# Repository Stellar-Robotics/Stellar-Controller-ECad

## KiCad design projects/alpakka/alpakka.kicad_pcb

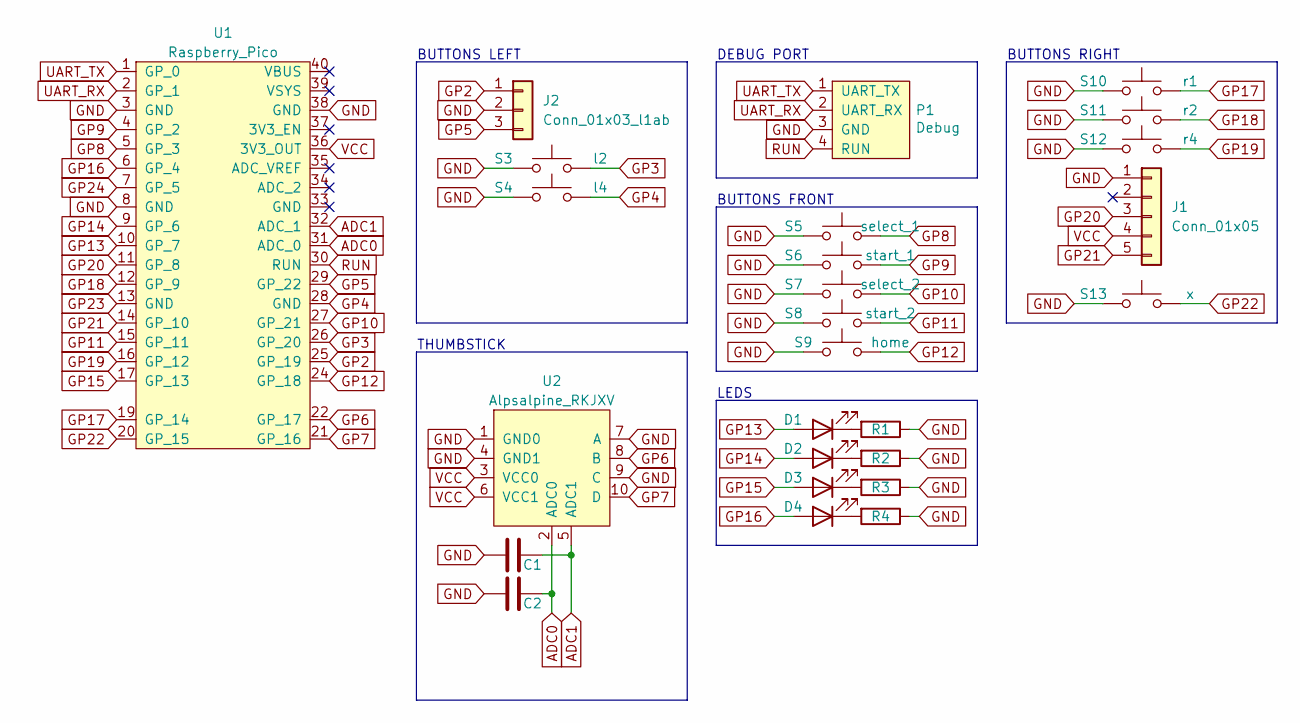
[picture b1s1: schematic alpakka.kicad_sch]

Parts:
C1, C2: C; 0402; LCSC C1525
D1, D2, D3, D4: Diode; 0603_d; LCSC C2290
J1: Conn_01x05; PinHeader_1x05_P2.54mm_Vertical
J2: Conn_01x03_l1ab; PinSocket_1x03_P2.54mm_Vertical
P1: Debug; JST_S4B-PH-SM4-K-TB; LCSC C265332
R1, R2, R3, R4: R; 0603; LCSC C22950
S3: l2; Alpsalpine_SKQG; LCSC C202424
S4: l4; Alpsalpine_SKQG; LCSC C202424
S5: select_1; Alpsalpine_SKPM; LCSC C115348
S6: start_1; Alpsalpine_SKPM; LCSC C115348
S7: select_2; Alpsalpine_SKPM; LCSC C115348
S8: start_2; Alpsalpine_SKPM; LCSC C115348
S9: home; Alpsalpine_SKPM; LCSC C115348
S10: r1; Alpsalpine_SKHHL; LCSC C125031
S11: r2; Alpsalpine_SKQG; LCSC C202424
S12: r4; Alpsalpine_SKQG; LCSC C202424
S13: x; Alpsalpine_SKPM; LCSC C115348
U1: Raspberry_Pico; LCSC C7203002
U2: Alpsalpine_RKJXV; Alpsalpine_RKJXV122400R; LCSC C918854

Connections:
ADC0: C2.2, U1.31 (ADC_0), U2.2 (ADC0)
ADC1: C1.2, U1.32 (ADC_1), U2.5 (ADC1)
GND: C1.1, C2.1, J1.1, J2.2, P1.3 (GND), R1.1, R2.1, R3.1, R4.1, S3.1, S4.1, S5.1, S6.1, S7.1, S8.1, S9.1, S10.1, S11.1, S12.1, S13.1, U1.3 (GND), U1.8 (GND), U1.38 (GND), U2.1 (GND0), U2.4 (GND1), U2.7 (A), U2.9 (C)
GP2: J2.1, U1.25 (GP_19)
GP3: S3.2, U1.26 (GP_20)
GP4: S4.2, U1.28 (GND)
GP5: J2.3, U1.29 (GP_22)
GP6: U1.22 (GP_17), U2.8 (B)
GP7: U1.21 (GP_16), U2.10 (D)
GP8: S5.2, U1.5 (GP_3)
GP9: S6.2, U1.4 (GP_2)
GP10: S7.2, U1.27 (GP_21)
GP11: S8.2, U1.15 (GP_11)
GP12: S9.2, U1.24 (GP_18)
GP13: D1.2 (A), U1.10 (GP_7)
GP14: D2.2 (A), U1.9 (GP_6)
GP15: D3.2 (A), U1.17 (GP_13)
GP16: D4.2 (A), U1.6 (GP_4)
GP17: S10.2, U1.19 (GP_14)
GP18: S11.2, U1.12 (GP_9)
GP19: S12.2, U1.16 (GP_12)
GP20: J1.3, U1.11 (GP_8)
GP21: J1.5, U1.14 (GP_10)
GP22: S13.2, U1.20 (GP_15)
GP23: U1.13 (GND)
GP24: U1.7 (GP_5)
unnamed: D1.1 (K), R1.2
unnamed: D2.1 (K), R2.2
unnamed: D3.1 (K), R3.2
unnamed: D4.1 (K), R4.2
RUN: P1.4 (RUN), U1.30 (RUN)
UART_RX: P1.2 (UART_RX), U1.2 (GP_1)
UART_TX: P1.1 (UART_TX), U1.1 (GP_0)
VCC: J1.4, U1.36 (3V3_OUT), U2.3 (VCC0), U2.6 (VCC1)

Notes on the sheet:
DEBUG PORT
THUMBSTICK
BUTTONS FRONT
LEDS
BUTTONS LEFT
BUTTONS RIGHT

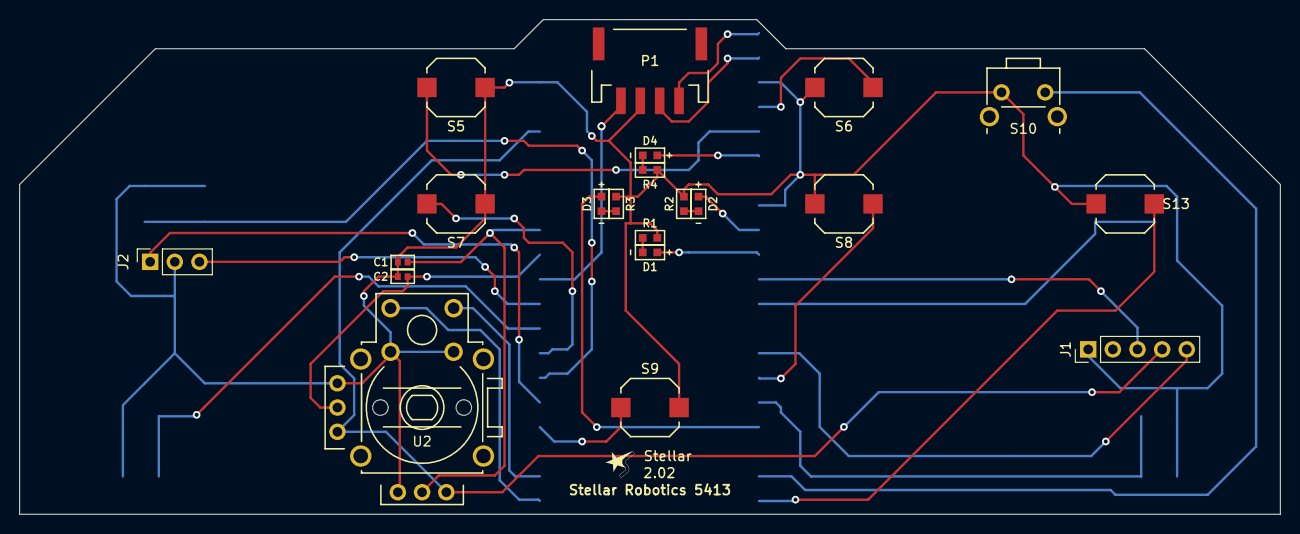
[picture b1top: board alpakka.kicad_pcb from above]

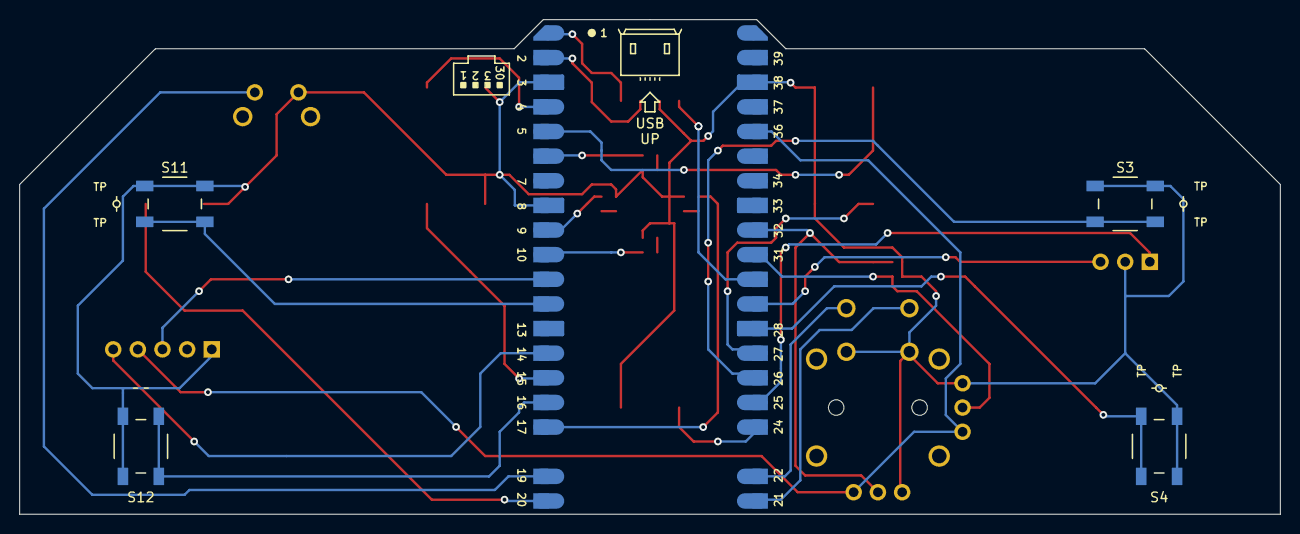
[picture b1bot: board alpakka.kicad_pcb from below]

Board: 2 copper layers, 130.0 x 51.0 mm, 26 parts (5 on the bottom side), 32 nets.

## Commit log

2026-03-15 final version of pcb from 2025
